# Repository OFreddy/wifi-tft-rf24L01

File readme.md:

# WifiDisplay

A project for communicating with Hoymiles solar inverters combined with the option to display different values on a 2.4 inch TFT display. 

## Preface
Inspired from the [discussion](https://www.mikrocontroller.net/topic/525778) on (Mikrocontroller.net) I also started investigating on protocol and communication details. With [this](https://www.mikrocontroller.net/topic/525778?page=single#7014857)
 post a first contact to the inverters was the base for several projects.
I wanted an independent display to always have an overview of the current yield data in a simple and clear manner.

This project is still a work in progress. It is far away from the almost perfect and comfortable and easy to use solutions from other projects. 

Some more pictures of the latest prototype can be found [here](docs/images/README.md).
---
## Firmware

The firmware for the EPS8266 microcontroller is build with Arduino PlatformIO Framework for the ESP8266. 

It uses a snapshot or a fork of the following projects:

- [ThingPulse minigrafx](https://github.com/ThingPulse/minigrafx)
- [Bounce2](https://github.com/thomasfredericks/Bounce2)
- [RobTillaart CRC](https://github.com/RobTillaart/CRC)
- [BuelowP sunset](https://github.com/buelowp/sunset)

and some more (experimental)...

---
## Hardware - Required components and material 

### ESP8266 WeMos D1 mini

As controller platform a WeMos D1 mini compatible ESP8266 board is required.

Sample picture

Source of supply
[Makershop](https://www.makershop.de/plattformen/d1-mini/esp8266-mini-board/)
[AZ-Delivery](https://www.az-delivery.de/products/d1-mini)

### NRF24L01+ radio board with external antenna

Sample picture

### ILI9341 based TFT Display 320x240 pixel

I always order the TFT modules directly from China via AliExpress. As the suppliers change frequently it is difficult to keep a link updated here. Make sure the pcb has the dimensions 77mm x 42.5mm and a 14 pin header at the bottom for target connection.

**Sample picture**

### BOM for the pcb
|Quantity|Item|
|--------|----|
|2 pc.|socket strip 8x1 pin 6mm heigth 2.56mm pitch|
|1 pc.|socket strip 4x2 pin 2.56mm pitch|
|1 pc.|socket strip 8x1 pin 8mm height 2.56mm pitch|
|1 pc.|pin header 2x1 pin 2.56mm pitch|
|1 pc.|Polarized capacitor 100uF 35V 2.56mm pitch|
|1 pc.|Capacitor SMD 100nF 0603|
|1 pc.|Resistor SMD 10k 0603|
|1 pc.|Resistor SMD 1k 0603|

### Other components and mounting material

**A tact Button Switch 6 x 6 x 4.3 mm**

The switch is used for different options when interacting with the display application. It is mounted inside the housing using the 3D printed mount. The pins of the switch must be bent straight and put through the small holes in the holder as shown on this picture.

|Quantity|Item|
|--------|----|
|4 pc.|Countersunk screw M3 x 5mm|
|6 pc.|Washer 3.2mm|
|4 pc.|Cylinder head screw M3 x 8mm|
|4 pc.|Nuts M3|

---
## Further documentation

### Connection Summary for ILI9341 TFT Display:

ESP8266       -> ILI9341
Vin           -> Vcc        (red)
GND           -> GND        (black)
GPIO 15  (D8) -> CS         (violett)
GPIO 2   (D4) -> RESET      (brown)
GPIO 4   (D2) -> D/C        (gray)
GPIO 13  (D7) -> SDI(MOSI)  (green)
GPIO 14  (D5) -> SCK        (yellow)
GPIO 5   (D1) -> LED        (orange)
GPIO 12  (D6) -> SDO(MISO)  (spare)

---
## Related Projects
- [OpenDTU](https://github.com/tbnobody/OpenDTU)
- [Ahoy](https://github.com/grindylow/ahoy)
- [DTU Simulator](https://github.com/Ziyatoe/DTUsimMI1x00-Hoymiles)
- [OpenDTU extended to talk to Victrons MPPT battery chargers (Ve.Direct)](https://github.com/helgeerbe/OpenDTU_VeDirect)
- [BreakoutBoard - sample printed circuit board for OpenDTU and Ahoy](https://github.com/dokuhn/openDTU-BreakoutBoard)

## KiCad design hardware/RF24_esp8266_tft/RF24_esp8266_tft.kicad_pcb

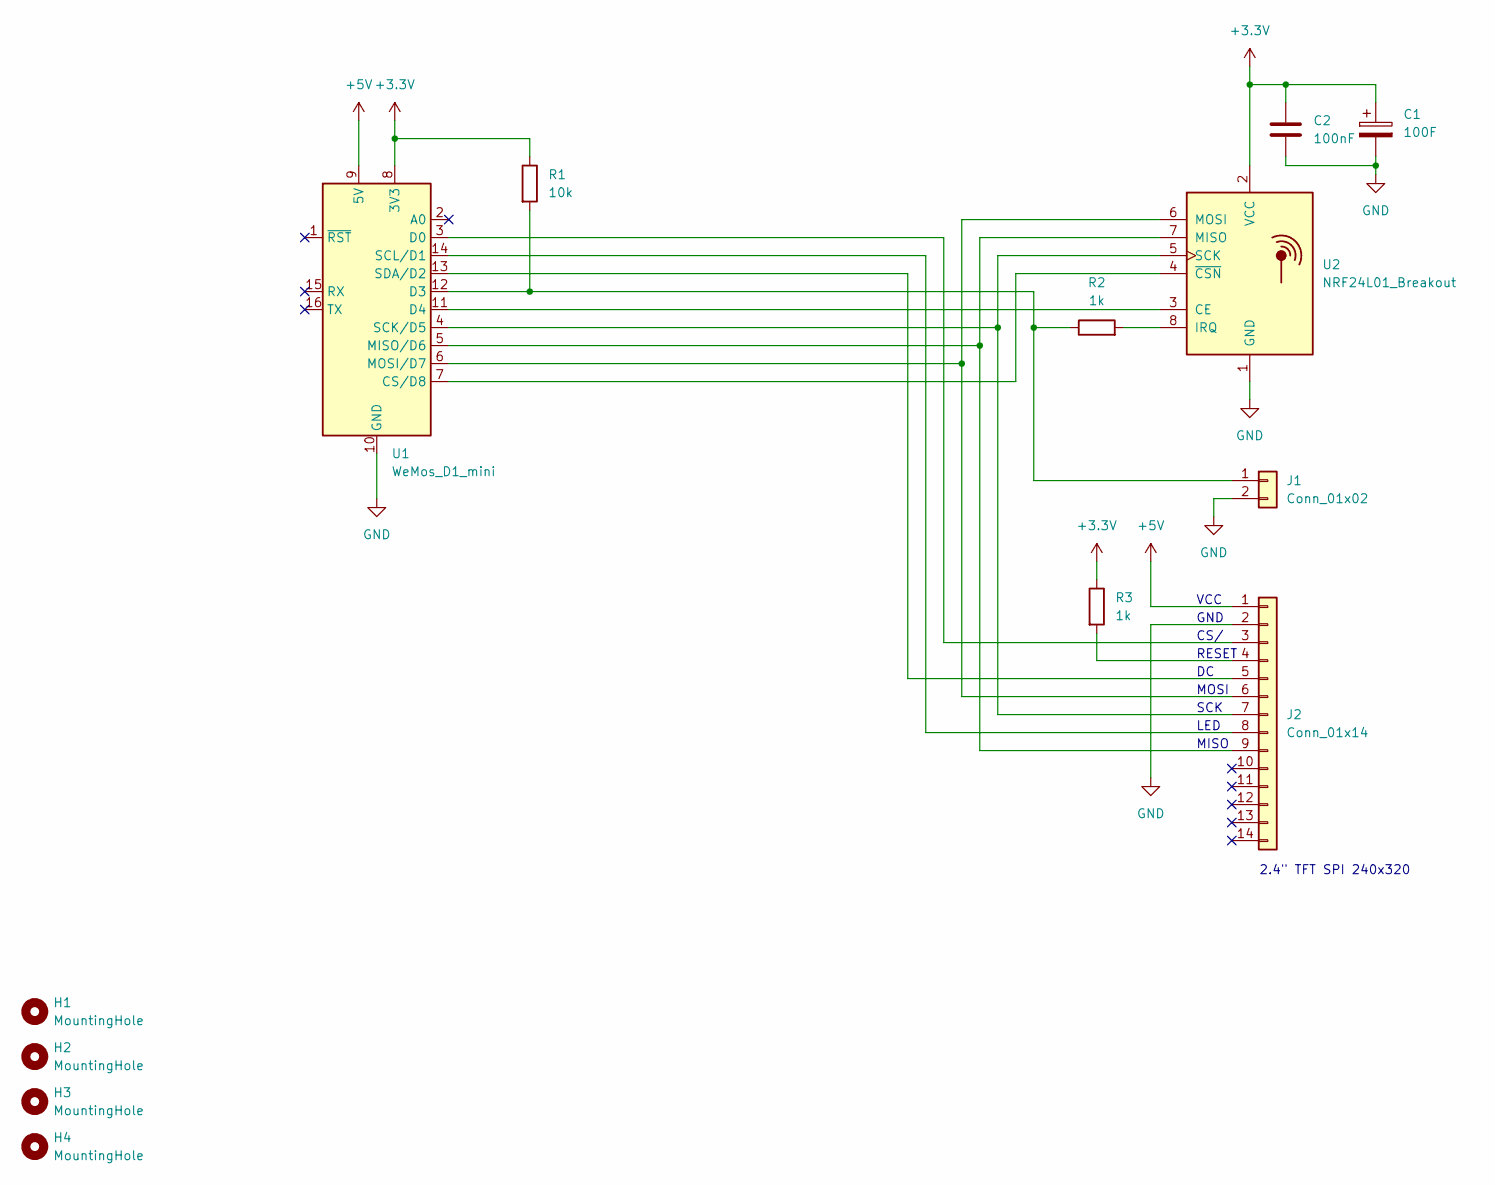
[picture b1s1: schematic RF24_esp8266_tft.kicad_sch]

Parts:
C1: 100F; CP_Radial_D5.0mm_P2.50mm
C2: 100nF; C_0201_0603Metric_Pad0.64x0.40mm_HandSolder
H1, H2, H3, H4: MountingHole; MountingHole_3.2mm_M3_DIN965
J1: Conn_01x02; PinHeader_1x02_P2.54mm_Vertical
J2: Conn_01x14; PinHeader_1x14_P2.54mm_Vertical
R1: 10k; R_0603_1608Metric_Pad0.98x0.95mm_HandSolder
R2, R3: 1k; R_0603_1608Metric_Pad0.98x0.95mm_HandSolder
U1: WeMos_D1_mini; WEMOS_D1_mini_light
U2: NRF24L01_Breakout; nRF24L01_Breakout

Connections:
+3.3V: C1.1, C2.1, R1.1, R3.1, U1.8 (3V3), U2.2 (VCC)
+5V: J2.1, U1.9 (5V)
GND: C1.2, C2.2, J1.2, J2.2, U1.10 (GND), U2.1 (GND)
unnamed: J1.1, R1.2, R2.1, U1.12 (D3)
unnamed: J2.3, U1.3 (D0)
unnamed: J2.4, R3.2
unnamed: J2.5, U1.13 (SDA/D2)
unnamed: J2.6, U1.6 (MOSI/D7), U2.6 (MOSI)
unnamed: J2.7, U1.4 (SCK/D5), U2.5 (SCK)
unnamed: J2.8, U1.14 (SCL/D1)
unnamed: J2.9, U1.5 (MISO/D6), U2.7 (MISO)
unnamed: R2.2, U2.8 (IRQ)
unnamed: U1.7 (CS/D8), U2.4 (~CSN)
unnamed: U1.11 (D4), U2.3 (CE)

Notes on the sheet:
CS/
2.4" TFT SPI 240x320
VCC
MOSI
SCK
RESET
MISO
LED
GND

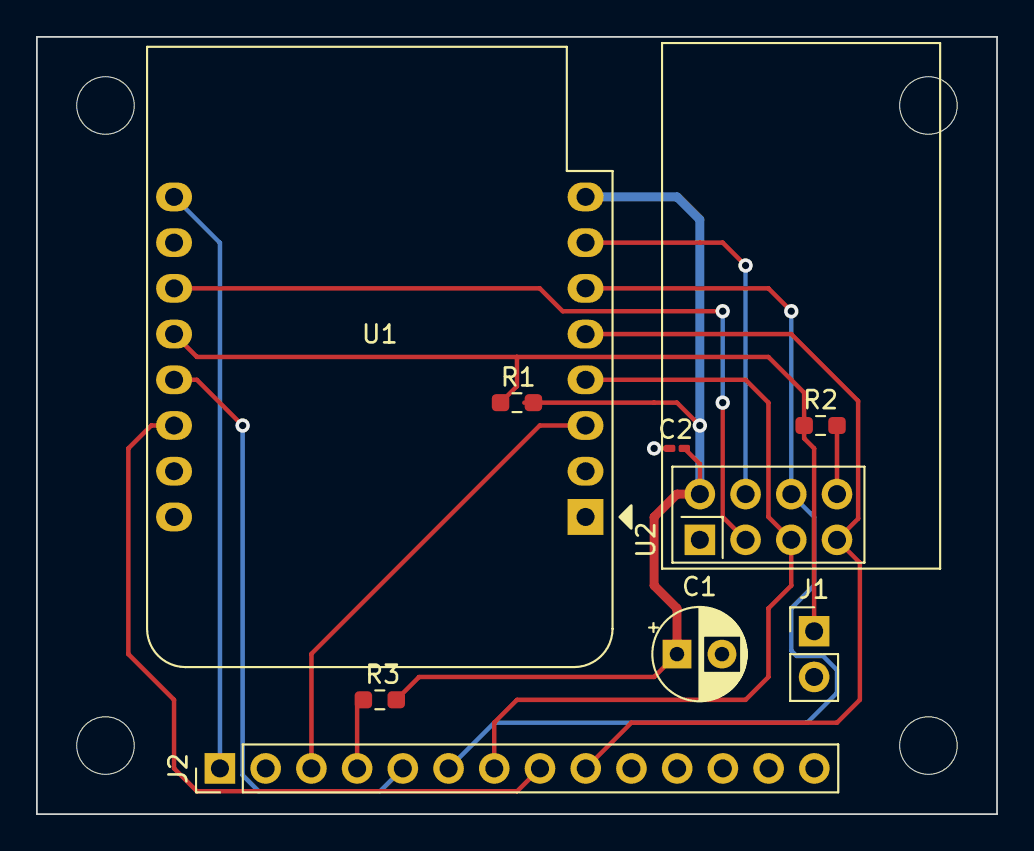
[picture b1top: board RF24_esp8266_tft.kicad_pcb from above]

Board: 2 copper layers, 53.3 x 43.2 mm, 13 parts (0 on the bottom side), 14 nets.

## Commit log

2022-12-25 wip save
2023-01-03 HTTPRESPONSE_TIMEOUT
2023-01-24 Cleanup / Added revised model for Housing
    Bugfix SunsetClass
    Moved library minigrafx to custom fork
2023-02-19 Save WIP
2024-12-08 Updated ENV_STR to new powermeter
2025-03-01 Update Lib Deps
